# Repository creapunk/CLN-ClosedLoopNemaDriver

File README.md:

# CLN17 - CLOSED-LOOP DRIVER FOR NEMA17

[CLN17 cncept video](http://www.youtube.com/watch?v=A67UROq0t6Q)

# Project Overview

The CLN17 motor driver is an **open-source**, compact, high-performance closed-loop stepper motor driver designed specifically for NEMA17 form factor motors. The driver offers advanced features such as silent and smooth motion, high-precision position control, and energy-saving capabilities, making it ideal for various applications, including robotics, CNC machines, and 3D printers. 

Detailed documentation at [creapunk.com](https://creapunk.com)!

## Board Diagram

## Key Features

- 🕹️ **Closed-Loop Control:** Enables precise motion in challenging conditions.
- 💪 **Adaptive Torque Control:** Optimizes energy efficiency, reduces stress, and extends motor lifespan.
- 🧩 **Reliable Operation and Enhanced Safety:** Ensures reliable operation and protects users from potential harm.
- 🛡️ **Modular Concept:** Provides flexibility and cost-effectiveness through various configurations and expansion boards.

## Key Specs

- 🔌 **Wide Input Voltage Range:** 5-25VDC with reverse polarity and surge protection
- ⚡️ **Powerful Motor Control:** 1.4A RMS current per phase with up to 2.5A peak and up to 1/256 microstepping
- 🚀 **High-Performance MCU:** STM32G431CB Arm Cortex-M4 running at 170MHz with Classic EN/DIR/STEP interface, CAN-Bus, I2C, UART and USB Type-C with PD2.0 support,
- 🔒 **Compact and Durable Design:** 38x38mm PCB, with optional aluminum housing for heat dissipation and mechanical protection and minimal height of 7.5mm (10mm with connectors)

## Applications

- 🎓 Learning Platforms
- 🛠️ CNC Machines & 3D printers
- 🤖 Robotics & Automation Systems
- 🤝 Collaborative Robots
- 🔭 Camera & Telescope Stabilization Systems
- 🔬 Laboratory Equipment
- 🏭 Industrial Motion Control Systems
- 📳 Haptics & Force Feedback Systems

------

### Support the Project!

**If you like the project and want to support its development, you can do so through:**

- **[Ko-fi](https://ko-fi.com/creapunk)** (*preferred for membership subscription and one-time donation*) - here, you can sign up for monthly support, or you can make a one-time donation as well!
- **[Patreon](http://patreon.com/creapunk)** - similar to Ko-fi, but with higher fees.

Don't forget to join **[creapunk community on Discord](https://discord.gg/4uFSsffhMt)** for the latest updates and discussions!

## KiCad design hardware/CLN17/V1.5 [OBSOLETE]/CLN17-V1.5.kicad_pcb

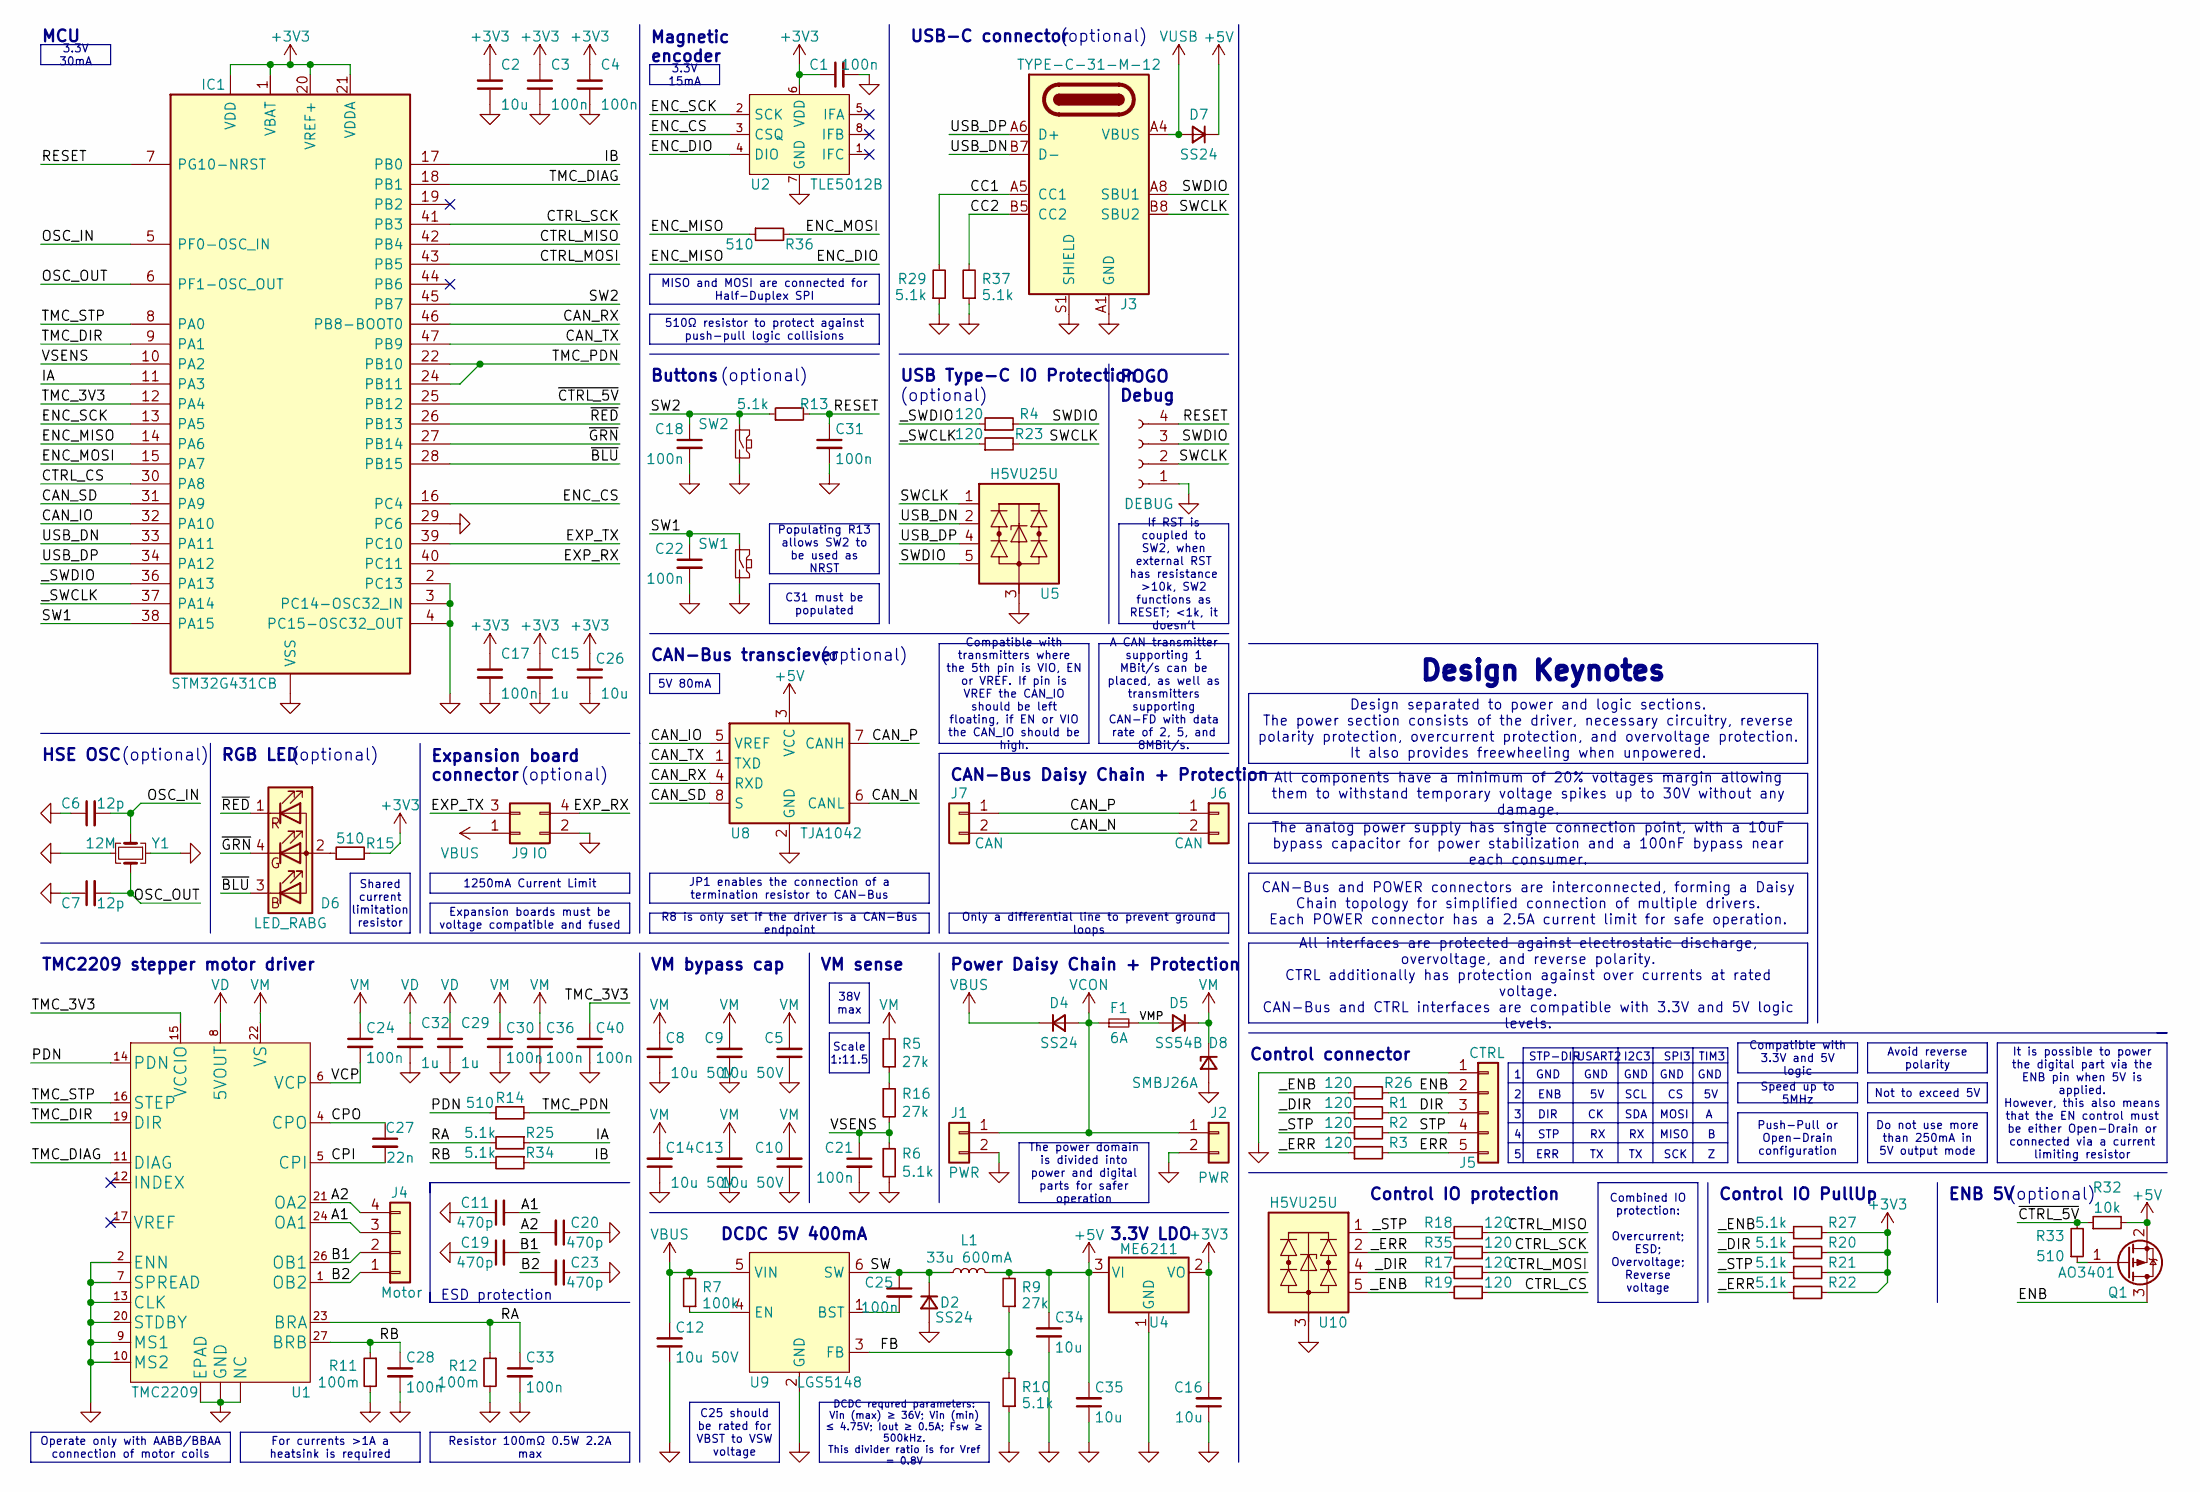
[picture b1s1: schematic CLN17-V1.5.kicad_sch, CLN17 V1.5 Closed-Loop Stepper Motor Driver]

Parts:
C1, C3, C4, C17, C18, C21, C22, C24, C28, C30, C31, C33, C36, C40: 100n; C0402; Part Type Basic; LCSC Part # C307331
C2, C16, C26, C34, C35: 10u; C0402; Part Type Basic; LCSC Part # C15525
C5, C8, C9, C10, C12, C13, C14: 10u 50V; C_1206_3216Metric; Part Type Basic; LCSC Part # C13585
C6, C7: 12p; C0402; Part Type Basic; LCSC Part # C1547
C11, C19, C20, C23: 470p; C0402; Part Type Basic; LCSC Part # C1537
C15, C29, C32: 1u; C0402; Part Type Basic; LCSC Part # C52923
C25: 100n; C0402; Part Type Basic; LCSC Part # C1525
C27: 22n; C0402; Part Type Basic; LCSC Part # C1532
D2, D4, D7: SS24; D_SOD-123F; Part Type Extended; LCSC Part # C2827931
D5: SS54B; D_SMB; Part Type Extended; LCSC Part # C3011125
D6: LED_RABG; LED_RGB_0606; Part Type Extended; LCSC Part # C2874115
D8: SMBJ26A; D_SMB; Part Type Extended; LCSC Part # C726831
F1: 6A; R1206_Shunt; Part Type Extended; LCSC Part # C183157
IC1: STM32G431CB; QFN-48-1EP_7x7mm_P0.5mm_EP5.6x5.6mm; Part Type Extended; LCSC Part # C529356
J1, J2: PWR; XH2.54 2P; Part Type Extended; LCSC Part # C2908611
J3: TYPE-C-31-M-12; USB-TYPE-C-31-M-12; Part Type Extended; LCSC Part # C2988369
J4: Motor; XH2.54 4P; Part Type Extended; LCSC Part # C21273
J5: CTRL; PH2.0 5P; Part Type Extended; LCSC Part # C2908637
J6, J7: CAN; PH2.0 2P; Part Type Extended; LCSC Part # C2908634
J8: DEBUG; SWD; Part Type -----
J9: IO; 2x2P2.00mm_Vertical_SMD; Part Type Extended; LCSC Part # C2911301
L1: 33u 600mA; CD32; Part Type Extended; LCSC Part # C492262
Q1: AO3401; SOT-23-3; Part Type Basic; LCSC Part # C15127
R1, R2, R3, R4, R17, R18, R19, R23, R26, R35: 120; R0402; Part Type Basic; LCSC Part # C25079
R5, R9, R16: 27k; R0402; Part Type Basic; LCSC Part # C25771
R6, R10, R13, R20, R21, R22, R25, R27, R29, R34, R37: 5.1k; R0402; Part Type Basic; LCSC Part # C25941
R7: 100k; R0402; Part Type Basic; LCSC Part # C25741
R11, R12: 100m; R1206_Shunt; Part Type Extended; LCSC Part # C7467250
R14, R15, R33, R36: 510; R0402; Part Type Basic; LCSC Part # C25123
R32: 10k; R0402; Part Type Basic; LCSC Part # C25744
SW1, SW2: SW_Push; SW_SPST_PTS810; Part Type Extended; LCSC Part # C2888427
U1: TMC2209; QFN-28-termal; Part Type Extended; LCSC Part # C465949
U2: TLE5012B; SOIC-8_3.9x4.9mm_P1.27mm; Part Type Extended; LCSC Part # C123083
U4: ME6211; SOT-23-3; Part Type Basic; LCSC Part # C168807
U5, U10: H5VU25U; DFN-2510; Part Type Basic; JLC Rotation Offset 270
U8: TJA1042; HVSON-8-1EP_3x3mm_P0.65mm_EP1.6x2.4mm; Part Type Extended; LCSC Part # C131480
U9: LGS5148; SOT-23-6; Part Type Extended; LCSC Part # C5123972
Y1: 12M; Crystal-3225-4P; Part Type Basic; LCSC Part # C9002

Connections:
+3V3: C1.1, C2.2, C3.1, C4.1, C15.1, C16.2, C17.1, C26.2, IC1.1 (VBAT), IC1.20 (VREF+), IC1.21 (VDDA), IC1.23 (VDD), IC1.35 (VDD), IC1.48 (VDD), R15.2, R20.2, R21.2, R22.2, R27.2, U2.6 (VDD), U4.2 (VO)
+5V: C34.2, C35.2, D7.1 (K), L1.2, Q1.2 (S), R9.2, R32.2, U4.3 (VI), U8.3 (VCC)
/A1: C11.2, J4.3, U1.24 (OA1)
/A2: C20.2, J4.4, U1.21 (OA2)
/B1: C19.2, J4.2, U1.26 (OB1)
/B2: C23.2, J4.1, U1.1 (OB2)
/CAN_IO: IC1.32 (PA10), U8.5 (VREF)
/CAN_N: J6.2, J7.2, U8.6 (CANL)
/CAN_P: J6.1, J7.1, U8.7 (CANH)
/CAN_RX: IC1.46 (PB8-BOOT0), U8.4 (RXD)
/CAN_SD: IC1.31 (PA9), U8.8 (S)
/CAN_TX: IC1.47 (PB9), U8.1 (TXD)
/CC1: J3.A5 (CC1), R29.2
/CC2: J3.B5 (CC2), R37.2
/CPI: C27.2, U1.5 (CPI)
/CPO: C27.1, U1.4 (CPO)
/CTRL_CS: IC1.30 (PA8), R19.1
/CTRL_MISO: IC1.42 (PB4), R18.1
/CTRL_MOSI: IC1.43 (PB5), R17.1
/CTRL_SCK: IC1.41 (PB3), R35.1
/DIR: J5.3, R1.2
/ENB: J5.2, Q1.3 (D), R26.2
/ENC_CS: IC1.16 (PC4), U2.3 (CSQ)
/ENC_DIO: IC1.14 (PA6), R36.1, U2.4 (DIO)
/ENC_MOSI: IC1.15 (PA7), R36.2
/ENC_SCK: IC1.13 (PA5), U2.2 (SCK)
/ERR: J5.5, R3.2
/EXP_RX: IC1.40 (PC11), J9.4
/EXP_TX: IC1.39 (PC10), J9.3
/FB: R9.1, R10.2, U9.3 (FB)
/IA: IC1.11 (PA3), R25.1
/IB: IC1.17 (PB0), R34.1
/OSC_IN: C6.2, IC1.5 (PF0-OSC_IN), Y1.1
/OSC_OUT: C7.2, IC1.6 (PF1-OSC_OUT), Y1.3
/PDN: R14.1, U1.14 (PDN)
/RA: C33.1, R12.1, R25.2, U1.23 (BRA)
/RB: C28.1, R11.1, R34.2, U1.27 (BRB)
/RESET: C31.1, IC1.7 (PG10-NRST), J8.4, R13.2
/STP: J5.4, R2.2
/SW: C25.1, D2.1 (K), L1.1, U9.6 (SW)
/SW1: C22.1, IC1.38 (PA15), SW1.1
/SW2: C18.1, IC1.45 (PB7), R13.1, SW2.1
/SWCLK: J3.B8 (SBU2), J8.2, R23.2, U5.1 (I/O1), U5.10
/SWDIO: J3.A8 (SBU1), J8.3, R4.2, U5.5 (I/O4), U5.6 (I/O4)
/TMC_3V3: C40.1, IC1.12 (PA4), U1.15 (VCCIO)
/TMC_DIAG: IC1.18 (PB1), U1.11 (DIAG)
/TMC_DIR: IC1.9 (PA1), U1.19 (DIR)
/TMC_PDN: IC1.22 (PB10), IC1.24 (PB11), R14.2
/TMC_STP: IC1.8 (PA0), U1.16 (STEP)
/USB_DN: IC1.33 (PA11), J3.A7 (D-), J3.B7 (D-), U5.2 (I/O2), U5.9 (I/O2)
/USB_DP: IC1.34 (PA12), J3.A6 (D+), J3.B6 (D+), U5.4 (I/O3), U5.7 (I/O3)
/VCP: C24.2, U1.6 (VCP)
/VMP: D5.2 (A), F1.2
/VSENS: C21.1, IC1.10 (PA2), R6.1, R16.2
/_DIR: R1.1, R17.2, R20.1, U10.4 (I/O3), U10.7 (I/O3)
/_ENB: R19.2, R26.1, R27.1, U10.5 (I/O4), U10.6 (I/O4)
/_ERR: R3.1, R22.1, R35.2, U10.2 (I/O2), U10.9 (I/O2)
/_STP: R2.1, R18.2, R21.1, U10.1 (I/O1), U10.10
/_SWCLK: IC1.37 (PA14), R23.1
/_SWDIO: IC1.36 (PA13), R4.1
/~BLU: D6.3 (BK), IC1.28 (PB15)
/~CTRL_5V: IC1.25 (PB12), R32.1, R33.2
/~GRN: D6.4 (GK), IC1.27 (PB14)
/~RED: D6.1 (RK), IC1.26 (PB13)
GND: C1.2, C2.1, C3.2, C4.2, C5.1, C6.1, C7.1, C8.1, C9.1, C10.1, C11.1, C12.1, C13.1, C14.1, C15.2, C16.1, C17.2, C18.2, C19.1, C20.1, C21.2, C22.2, C23.1, C26.1, C28.2, C29.2, C30.2, C31.2, C32.2, C33.2, C34.1, C35.1, C36.2, C40.2, D2.2 (A), D8.2 (A), IC1.2 (PC13), IC1.3 (PC14-OSC32_IN), IC1.4 (PC15-OSC32_OUT), IC1.29 (PC6), IC1.49 (VSS), J1.2, J2.2, J3.A1 (GND), J3.A12 (GND), J3.B1 (GND), J3.B12 (GND), J3.S1 (SHIELD), J5.1, J8.1, J9.2, R6.2, R10.1, R11.2, R12.2, R29.1, R37.1, SW1.2, SW2.2, U1.2 (ENN), U1.3 (GND), U1.7 (SPREAD), U1.9 (MS1), U1.10 (MS2), U1.13 (CLK), U1.18 (GND), U1.20 (STDBY), U1.25 (NC), U1.29 (EPAD), U2.7 (GND), U4.1 (GND), U5.3 (GND), U5.8 (GND), U8.2 (GND), U8.9 (GND), U9.2 (GND), U10.3 (GND), U10.8 (GND), Y1.2, Y1.4
unnamed: D6.2 (A), R15.1
unnamed: Q1.1 (G), R33.1
unnamed: R5.2, R16.1
unnamed: C25.2, U9.1 (BST)
unnamed: R7.1, U9.4 (EN)
VBUS: C12.2, D4.1 (K), J9.1, R7.2, U9.5 (VIN)
VCON: D4.2 (A), F1.1, J1.1, J2.1
VD: C29.1, C32.1, U1.8 (5VOUT)
VM: C5.2, C8.2, C9.2, C10.2, C13.2, C14.2, C24.1, C30.1, C36.1, D5.1 (K), D8.1 (K), R5.1, U1.22 (VS), U1.28 (VS)
VUSB: D7.2 (A), J3.A4 (VBUS), J3.A9 (VBUS), J3.B4 (VBUS), J3.B9 (VBUS)

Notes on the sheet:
Combined IO protection: Overcurrent; ESD; Overvoltage; Reverse voltage
Do not use more than 250mA in 5V output mode
3.3V 30mA
A CAN transmitter supporting 1 MBit/s can be placed, as well as transmitters supporting CAN-FD with data rate of 2, 5, and 8MBit/s.
If RST is coupled to SW2, when external RST has resistance >10k, SW2 functions as RESET; <1k, it doesn't
R8 is only set if the driver is a CAN-Bus endpoint
The power domain is divided into power and digital parts for safer operation
C31 must be populated
Speed up to 5MHz
Design separated to power and logic sections. The power section consists of the driver, necessary circuitry, reverse polarity protection, overcurrent protection, and overvoltage protection. It also provides freewheeling when unpowered.
JP1 enables the connection of a termination resistor to CAN-Bus
Shared current limitation resistor
Expansion boards must be voltage compatible and fused
Compatible with 3.3V and 5V logic
It is possible to power the digital part via the ENB pin when 5V is applied. However, this also means that the EN control must be either Open-Drain or connected via a current limiting resistor
C25 should be rated for VBST to VSW voltage
38V max
Scale 1:11.5
Compatible with transmitters where the 5th pin is VIO, EN or VREF. If pin is VREF the CAN_IO should be left floating, if EN or VIO the CAN_IO should be high.
3.3V 15mA
All interfaces are protected against electrostatic discharge, overvoltage, and reverse polarity. CTRL additionally has protection against over currents at rated voltage. CAN-Bus and CTRL interfaces are compatible with 3.3V and 5V logic levels.
5V 80mA
Populating R13 allows SW2 to be used as NRST
All components have a minimum of 20% voltages margin allowing them to withstand temporary voltage spikes up to 30V without any damage.
1250mA Current Limit
Push-Pull or Open-Drain configuration
Operate only with AABB/BBAA connection of motor coils
Resistor 100mΩ 0.5W 2.2A max
DCDC requred parameters: Vin (max) ≥ 36V; Vin (min) ≤ 4.75V; Iout ≥ 0.5A; Fsw ≥ 500kHz. This divider ratio is for Vref = 0.8V
Not to exceed 5V
510Ω resistor to protect against push-pull logic collisions
CAN-Bus and POWER connectors are interconnected, forming a Daisy Chain topology for simplified connection of multiple drivers. Each POWER connector has a 2.5A current limit for safe operation.
Only a differential line to prevent ground loops
The analog power supply has single connection point, with a 10uF bypass capacitor for power stabilization and a 100nF bypass near each consumer.
For currents >1A a heatsink is required
MISO and MOSI are connected for Half-Duplex SPI
Avoid reverse polarity
STP-DIR
CAN-Bus Daisy Chain + Protection
(optional)

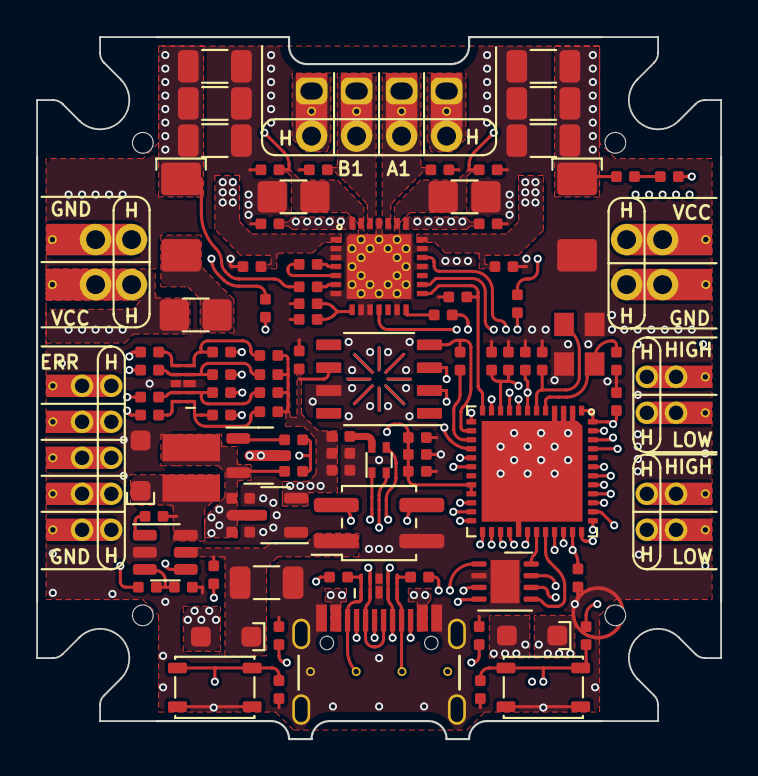
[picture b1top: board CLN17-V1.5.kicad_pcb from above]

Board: 4 copper layers, 38.0 x 39.0 mm, 98 parts (1 on the bottom side), 75 nets.

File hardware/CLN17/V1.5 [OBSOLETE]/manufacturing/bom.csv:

Designator,Footprint,Quantity,Value,LCSC Part #
"C1, C17, C18, C21, C22, C24, C28, C3, C30, C31, C33, C36, C4, C40",C0402,14,100n,C307331
"C10, C12, C13, C14, C5, C8, C9",1206,7,10u 50V,C13585
"C11, C19, C20, C23",C0402,4,470p,C1537
"C15, C29, C32",C0402,3,1u,C52923
"C16, C2, C26, C34, C35",C0402,5,10u,C15525
C25,C0402,1,100n,C1525
C27,C0402,1,22n,C1532
"C6, C7",C0402,2,12p,C1547
"D2, D4, D7",D_SOD-123F,3,SS24,C2827931
D5,D_SMB,1,SS54B,C3011125
D6,LED_RGB_0606,1,LED_RABG,C2874115
D8,D_SMB,1,SMBJ26A,C726831
F1,R1206_Shunt,1,6A,C183157
IC1,QFN-48-1EP_7x7mm_P0.5mm_EP5.6x5.6mm,1,STM32G431CB,C529356
"J1, J2",XH2.54 2P,2,PWR,C2908611
J3,USB-TYPE-C-31-M-12,1,TYPE-C-31-M-12,C2988369
J4,XH2.54 4P,1,Motor,C21273
J5,PH2.0 5P,1,CTRL,C2908637
"J6, J7",PH2.0 2P,2,CAN,C2908634
J9,2x2P2.00mm_Vertical_SMD,1,IO,C2911301
L1,CD32,1,33u 600mA,C492262
Q1,SOT-23-3,1,AO3401,C15127
"R1, R17, R18, R19, R2, R23, R26, R3, R35, R4",R0402,10,120,C25079
"R10, R13, R20, R21, R22, R25, R27, R29, R34, R37, R6",R0402,11,5.1k,C25941
"R11, R12",R1206_Shunt,2,100m,C7467250
"R14, R15, R33, R36",R0402,4,510,C25123
"R16, R5, R9",R0402,3,27k,C25771
R32,R0402,1,10k,C25744
R7,R0402,1,100k,C25741
"SW1, SW2",SW_SPST_PTS810,2,SW_Push,C2888427
U1,QFN-28-termal,1,TMC2209,C465949
"U10, U5",DFN-2510,2,H5VU25U,C7420374
U2,SOIC-8_3.9x4.9mm_P1.27mm,1,TLE5012B,C123083
U4,SOT-23-3,1,ME6211,C168807
U8,HVSON-8-1EP_3x3mm_P0.65mm_EP1.6x2.4mm,1,TJA1042,C131480
U9,SOT-23-6,1,LGS5148,C5123972
Y1,Crystal-3225-4P,1,12M,C9002

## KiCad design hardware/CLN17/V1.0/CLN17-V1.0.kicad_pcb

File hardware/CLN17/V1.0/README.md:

# CLN17 V1 Notes

> #### Attention!
>
> This board has been tested, and the functionality of its main components has been confirmed. However, the board has several issues.
>
> You can proceed with its production, but it's recommended to wait for the updated version with all corrections. By using these files, you acknowledge and understand that:
>
> - This version is released for preview purposes only and will not receive future support.
> - Any use of this version is at your own risk. The author is not responsible for any damage caused by the malfunction of this driver version.
> - Subsequent versions may have changes in the BoM and the layout of all board components, including connectors.

#### Known hardware issues:

- Unstable operation when powered from 4.5 to 5.7V. 
	Minor changes have been made to the circuit and the board that might theoretically fix this issue, but the problem may still arise. This might eliminate the possibility of powering solely through Type-C.
- NRST couldn't be reconfigured to function as a user button. This might be fixable through software.
- Incomplete UCPD interface

#### Known software issues:

- The CAN-Bus transceiver physically operates and produces a differential signal, but its software functionality hasn't been tested
- The IMU seems responsive, but the entire library might need to be rewritten for half-duplex SPI operation

#### Not tested:

- The operation of the external HSE crystal and the dependent RTC

#### V1.01 fixes [Nov 2023]:

- Optimised circuit power supply: 
	- Improved power polygon layout; 
	- Improved DCDC converter layout
- Improved Type-C compatibility: 
	- Added full-featured UCPD interface; 
	- Added 5.1k resistors in case UCPD doesn't work
- Optimised components:
	- ESD protection reduced form factor; 
	- Correct USB Type-C connector with both CC lines

#### V1.02 fixes [Dec 2023]:

- Changed 5V and 3.3V supply capacitor ratings from 2.2uF to 22uF
- Changed the crystal from 8MHz to 12MHz to be identical to V1.5 and V2. 
- Changed HSE load capacitors from 22pF to 12pF
- Removed IMU cause it was conflicting with encoder operation

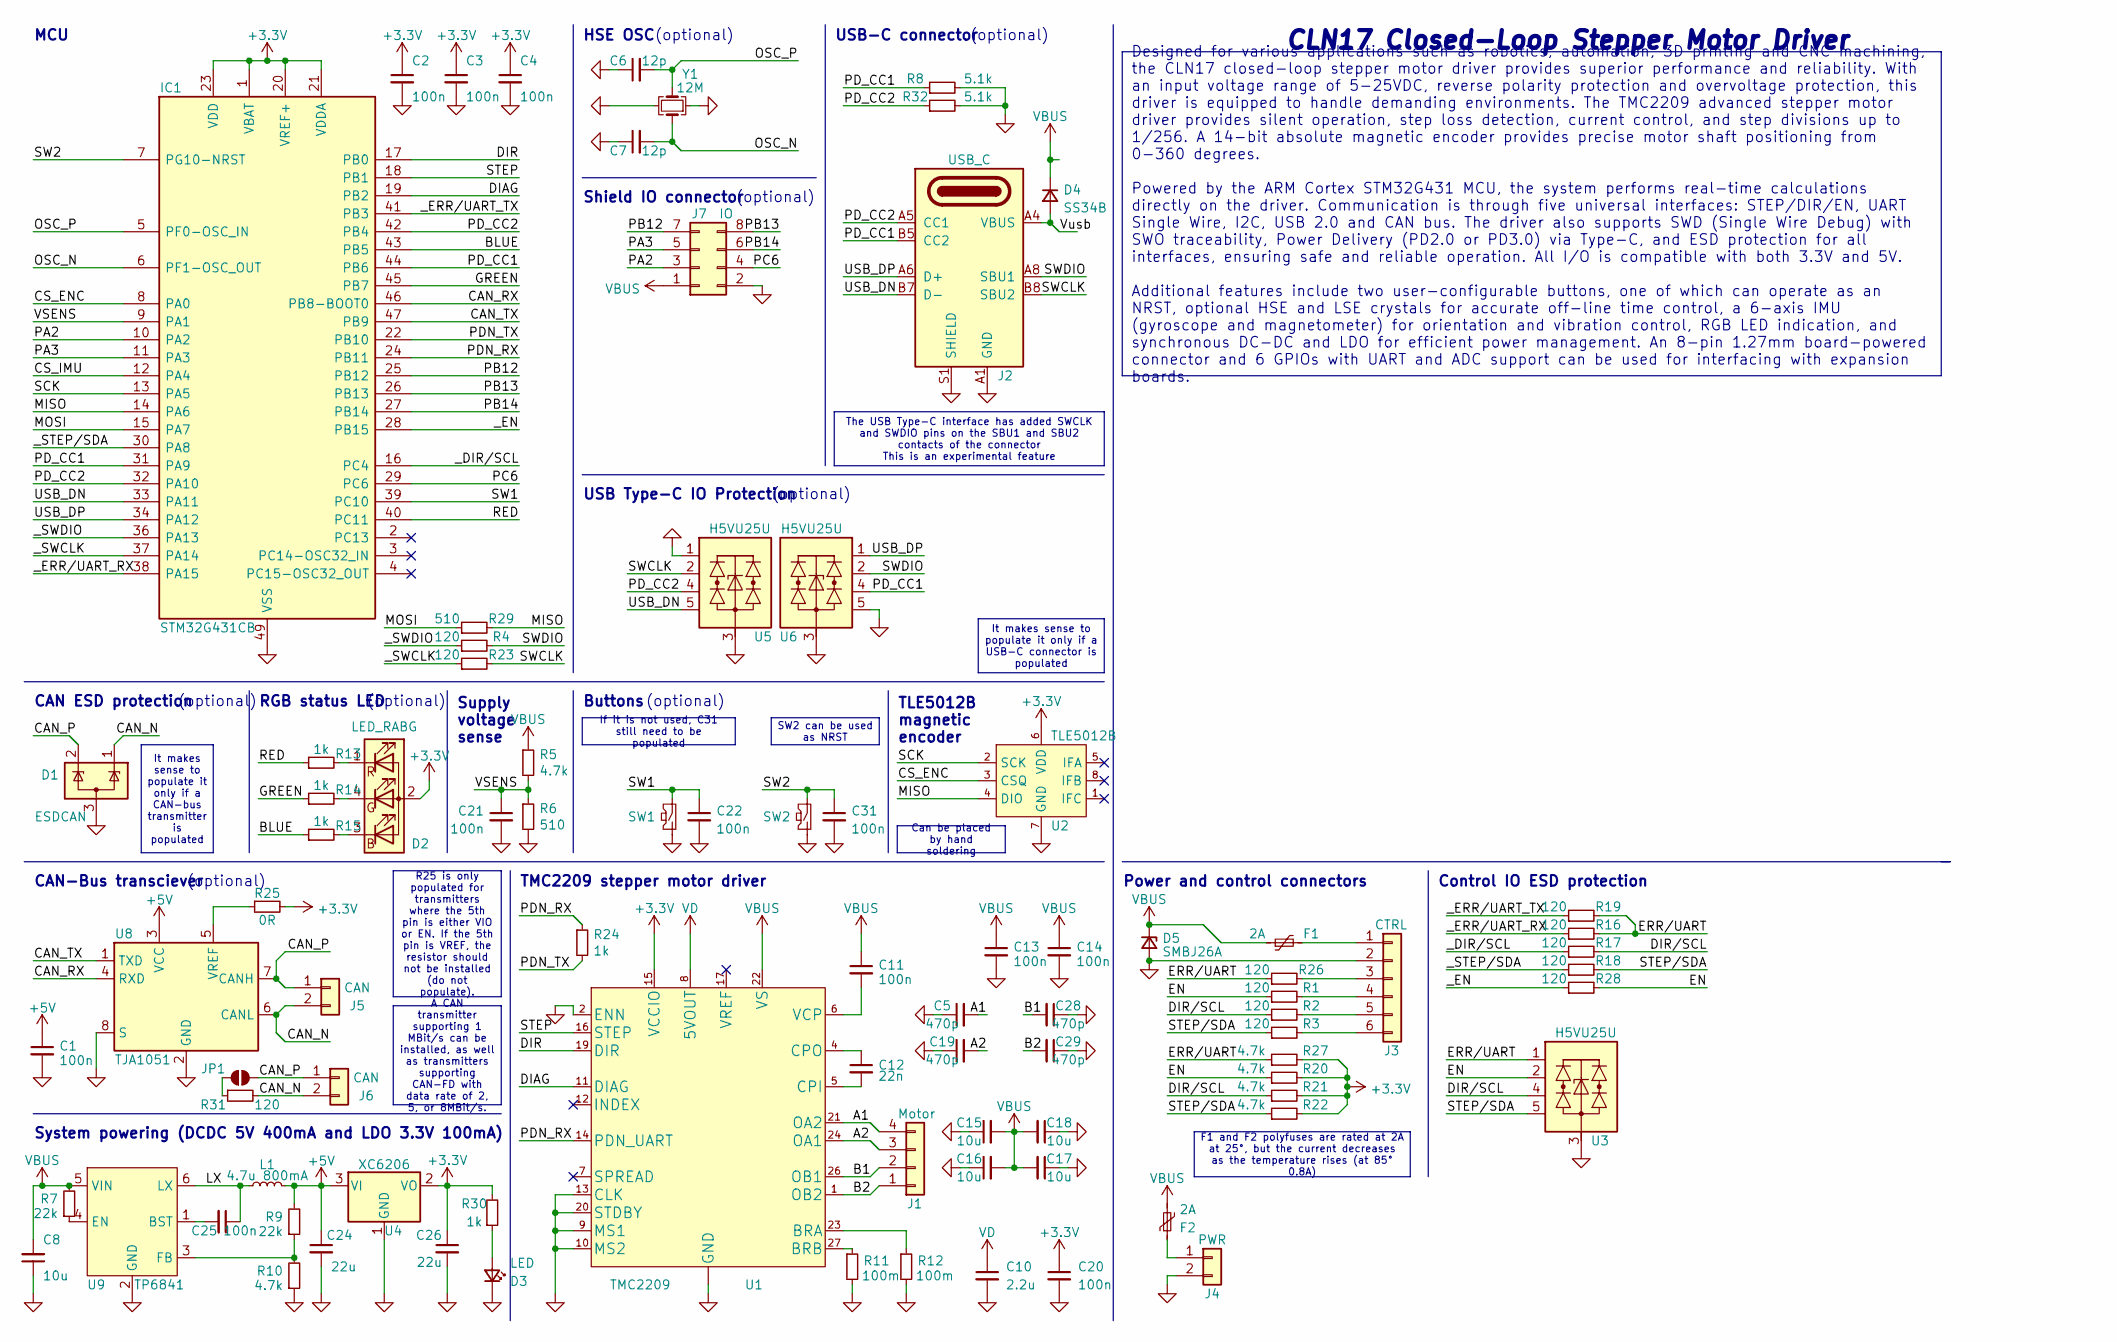
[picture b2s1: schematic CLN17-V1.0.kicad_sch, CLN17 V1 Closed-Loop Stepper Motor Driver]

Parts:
C1, C2, C3, C4, C11, C13, C14, C20, C21, C22, C25, C31: 100n; C0402; LCSC Part # C307331
C5, C19, C28, C29: 470p; C0402; LCSC Part # C1537
C6, C7: 12p; C0402; LCSC Part # C1547
C8, C15, C16, C17, C18: 10u; C_1206_3216Metric; LCSC Part # C13585
C10: 2.2u; C_0603_1608Metric; LCSC Part # C23630
C12: 22n; C0402; LCSC Part # C1532
C24, C26: 22u; C_0603_1608Metric; LCSC Part # C59461
D1: ESDCAN; SOT-23-3; LCSC Part # C2937021
D2: LED_RABG; LED_RGB_0606; LCSC Part # C2874115
D3: LED; LED_0603_1608Metric; LCSC Part # C72043
D4: SS34B; D_SMB; LCSC Part # C13762
D5: SMBJ26A; D_SMB; LCSC Part # C708006
F1, F2: 2A; Fuse_1812_4532Metric; LCSC Part # C960026
IC1: STM32G431CB; QFN-48-1EP_7x7mm_P0.5mm_EP5.6x5.6mm; LCSC Part # C529356
J1: Motor; XH2.54 4P; LCSC Part # C722872
J2: USB_C; USB-TYPE-C-31-M-12-SWD; LCSC Part # C963413
J3: CTRL; XH2.54 6P; LCSC Part # C722881
J4: PWR; XH2.54 2P; LCSC Part # C722860
J5, J6: CAN; PH2.0 2P; LCSC Part # C2908634
J7: IO; PinSocket_2x04_P1.27mm_Vertical; LCSC Part # C509139
JP1: SolderJumper_2_Open; SolderJumper
L1: 4.7u 800mA; L_0805_2012Metric; LCSC Part # C63166
R1, R2, R3, R4, R16, R17, R18, R19, R23, R26, R28, R31: 120; R0402; LCSC Part # C25079
R5, R10, R20, R21, R22, R27: 4.7k; R0402; LCSC Part # C25900
R6, R29: 510; R0402; LCSC Part # C25123
R7, R9: 22k; R0402; LCSC Part # C25768
R8, R32: 5.1k; R0402; LCSC Part # C25905
R11, R12: 100m; R_1206_3216Metric; LCSC Part # C25334
R13, R14, R15, R24, R30: 1k; R0402; LCSC Part # C11702
R25: 0R; R0402; LCSC Part # C17168
SW1, SW2: SW_Push; SW_SPST_PTS810; LCSC Part # C2888427
U1: TMC2209; QFN-28-termal; LCSC Part # C465949
U2: TLE5012B; SOIC-8_3.9x4.9mm_P1.27mm; LCSC Part # C123083
U3, U5, U6: H5VU25U; DFN-2510; JLC Rotation Offset 270
U4: XC6206; SOT-23-3; LCSC Part # C5446
U8: TJA1051; SOIC-8_3.9x4.9mm_P1.27mm; LCSC Part # C92211
U9: TP6841; SOT-23-6; LCSC Part # C2844736
Y1: 12M; Crystal-3225-4P; LCSC Part # C9002

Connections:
+3V3: C2.1, C3.1, C4.1, C20.1, C26.1, D2.2 (A), IC1.1 (VBAT), IC1.20 (VREF+), IC1.21 (VDDA), IC1.23 (VDD), IC1.35 (VDD), IC1.48 (VDD), R20.2, R21.2, R22.2, R25.2, R27.2, R30.2, U1.15 (VCCIO), U2.6 (VDD), U4.2 (VO)
+5V: C1.1, C24.1, L1.2, R9.2, U4.3 (VI), U8.3 (VCC)
/A1: C5.2, J1.4, U1.21 (OA2)
/A2: C19.2, J1.3, U1.24 (OA1)
/B1: C28.2, J1.2, U1.26 (OB1)
/B2: C29.2, J1.1, U1.1 (OB2)
/BLUE: IC1.43 (PB5), R15.1
/CAN_N: D1.1 (K), J5.2, J6.2, R31.2, U8.6 (CANL)
/CAN_P: D1.2 (K), J5.1, J6.1, JP1.2 (B), U8.7 (CANH)
/CAN_RX: IC1.46 (PB8-BOOT0), U8.4 (RXD)
/CAN_TX: IC1.47 (PB9), U8.1 (TXD)
/CS_ENC: IC1.8 (PA0), U2.3 (CSQ)
/CS_IMU: IC1.12 (PA4)
/DIAG: IC1.19 (PB2), U1.11 (DIAG)
/DIR: IC1.17 (PB0), U1.19 (DIR)
/DIR/SCL: R2.1, R17.2, R21.1, U3.4 (I/O3), U3.7 (I/O3)
/EN: R1.1, R20.1, R28.2, U3.2 (I/O2), U3.9 (I/O2)
/ERR/UART: R16.2, R19.2, R26.1, R27.1, U3.1 (I/O1), U3.10
/GREEN: IC1.45 (PB7), R14.1
/LX: C25.1, L1.1, U9.6 (LX)
/MISO: IC1.14 (PA6), R29.2, U2.4 (DIO)
/MOSI: IC1.15 (PA7), R29.1
/OSC_N: C7.2, IC1.6 (PF1-OSC_OUT), Y1.1
/OSC_P: C6.2, IC1.5 (PF0-OSC_IN), Y1.3
/PA2: IC1.10 (PA2), J7.3
/PA3: IC1.11 (PA3), J7.5
/PB12: IC1.25 (PB12), J7.7
/PB13: IC1.26 (PB13), J7.8
/PB14: IC1.27 (PB14), J7.6
/PC6: IC1.29 (PC6), J7.4
/PDN_RX: IC1.24 (PB11), R24.1, U1.14 (PDN_UART)
/PDN_TX: IC1.22 (PB10), R24.2
/PD_CC1: IC1.31 (PA9), IC1.44 (PB6), J2.B5 (CC2), R8.1, U6.4 (I/O3), U6.7 (I/O3)
/PD_CC2: IC1.32 (PA10), IC1.42 (PB4), J2.A5 (CC1), R32.1, U5.4 (I/O3), U5.7 (I/O3)
/RED: IC1.40 (PC11), R13.1
/SCK: IC1.13 (PA5), U2.2 (SCK)
/STEP: IC1.18 (PB1), U1.16 (STEP)
/STEP/SDA: R3.1, R18.2, R22.1, U3.5 (I/O4), U3.6 (I/O4)
/SW1: C22.1, IC1.39 (PC10), SW1.1
/SW2: C31.1, IC1.7 (PG10-NRST), SW2.1
/SWCLK: J2.B8 (SBU2), R23.2, U5.2 (I/O2), U5.9 (I/O2)
/SWDIO: J2.A8 (SBU1), R4.2, U6.2 (I/O2), U6.9 (I/O2)
/USB_DN: IC1.33 (PA11), J2.A7 (D-), J2.B7 (D-), U5.5 (I/O4), U5.6 (I/O4)
/USB_DP: IC1.34 (PA12), J2.A6 (D+), J2.B6 (D+), U6.1 (I/O1), U6.10
/VSENS: C21.1, IC1.9 (PA1), R5.2, R6.1
/Vusb: D4.2 (A), J2.A4 (VBUS), J2.A9 (VBUS), J2.B4 (VBUS), J2.B9 (VBUS)
/_DIR/SCL: IC1.16 (PC4), R17.1
/_EN: IC1.28 (PB15), R28.1
/_ERR/UART_RX: IC1.38 (PA15), R16.1
/_ERR/UART_TX: IC1.41 (PB3), R19.1
/_STEP/SDA: IC1.30 (PA8), R18.1
/_SWCLK: IC1.37 (PA14), R23.1
/_SWDIO: IC1.36 (PA13), R4.1
GND: C1.2, C2.2, C3.2, C4.2, C5.1, C6.1, C7.1, C8.1, C10.2, C13.2, C14.2, C15.1, C16.1, C17.1, C18.1, C19.1, C20.2, C21.2, C22.2, C24.2, C26.2, C28.1, C29.1, C31.2, D1.3 (A), D3.1 (K), D5.2 (A), IC1.49 (VSS), J2.A1 (GND), J2.A12 (GND), J2.B1 (GND), J2.B12 (GND), J2.S1 (SHIELD), J3.2, J4.2, J7.2, R6.2, R8.2, R10.1, R11.2, R12.2, R32.2, SW1.2, SW2.2, U1.2 (ENN), U1.3 (GND), U1.9 (MS1), U1.10 (MS2), U1.13 (CLK), U1.18 (GND), U1.20 (STDBY), U1.25 (NC), U1.29 (EPAD), U2.7 (GND), U3.3 (GND), U3.8 (GND), U4.1 (GND), U5.1 (I/O1), U5.3 (GND), U5.8 (GND), U5.10, U6.3 (GND), U6.5 (I/O4), U6.6 (I/O4), U6.8 (GND), U8.2 (GND), U8.8 (S), U9.2 (GND), Y1.2, Y1.4
unnamed: D2.3 (BK), R15.2
unnamed: D2.4 (GK), R14.2
unnamed: D2.1 (RK), R13.2
unnamed: D3.2 (A), R30.1
unnamed: F1.2, J3.1
unnamed: J3.3, R26.2
unnamed: J3.4, R1.2
unnamed: J3.5, R2.2
unnamed: J3.6, R3.2
unnamed: F2.1, J4.1
unnamed: JP1.1 (A), R31.1
unnamed: R12.1, U1.23 (BRA)
unnamed: R11.1, U1.27 (BRB)
unnamed: C12.2, U1.5 (CPI)
unnamed: C12.1, U1.4 (CPO)
unnamed: C11.2, U1.6 (VCP)
unnamed: R25.1, U8.5 (VREF)
unnamed: C25.2, U9.1 (BST)
unnamed: R7.1, U9.4 (EN)
unnamed: R9.1, R10.2, U9.3 (FB)
VBUS: C8.2, C11.1, C13.1, C14.1, C15.2, C16.2, C17.2, C18.2, D4.1 (K), D5.1 (K), F1.1, F2.2, J7.1, R5.1, R7.2, U1.22 (VS), U1.28 (VS), U9.5 (VIN)
VD: C10.1, U1.8 (5VOUT)

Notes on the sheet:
R25 is only populated for transmitters where the 5th pin is either VIO or EN. If the 5th pin is VREF, the resistor should not be installed (do not populate).
Can be placed by hand soldering
A CAN transmitter supporting 1 MBit/s can be installed, as well as transmitters supporting CAN-FD with data rate of 2, 5, or 8MBit/s.
If it is not used, C31 still need to be populated
The USB Type-C interface has added SWCLK and SWDIO pins on the SBU1 and SBU2 contacts of the connector This is an experimental feature
It makes sense to populate it only if a CAN-bus transmitter is populated
SW2 can be used as NRST
F1 and F2 polyfuses are rated at 2A at 25°, but the current decreases as the temperature rises (at 85° 0.8A)
It makes sense to populate it only if a USB-C connector is populated
Designed for various applications such as robotics, automation, 3D printing and CNC machining, the CLN17 closed-loop stepper motor driver provides superior performance and reliability. With an input voltage range of 5-25VDC, reverse polarity protection and overvoltage protection, this driver is equ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
(optional)
CLN17 Closed-Loop Stepper Motor Driver
TLE5012B magnetic encoder
MCU
CAN-Bus transciever
Power and control connectors
System powering (DCDC 5V 400mA and LDO 3.3V 100mA)
CAN ESD protection
Shield IO connector
USB-C connector
TMC2209 stepper motor driver
Buttons
RGB status LED
Supply voltage sense
HSE OSC
Control IO ESD protection
USB Type-C IO Protection

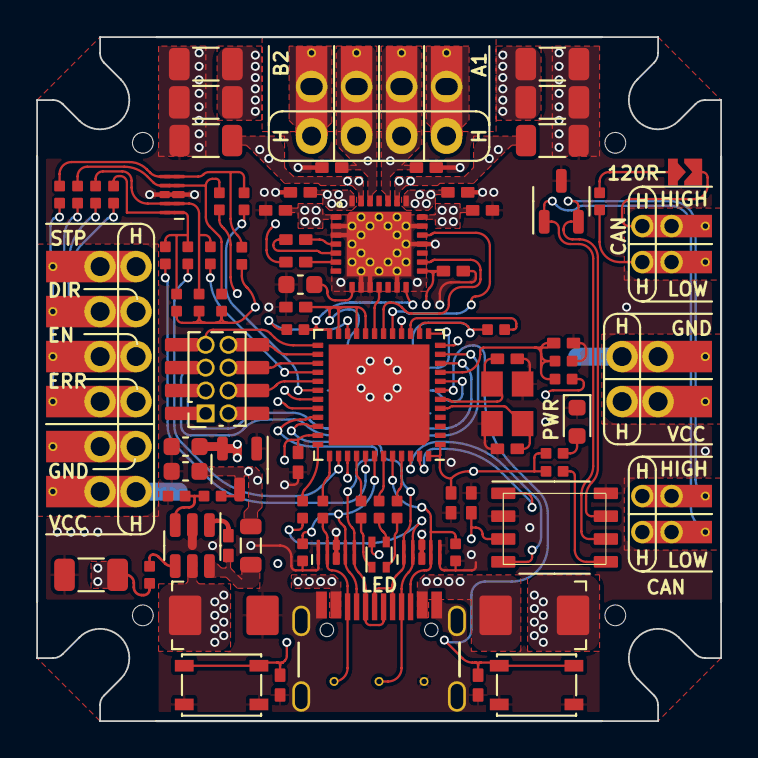
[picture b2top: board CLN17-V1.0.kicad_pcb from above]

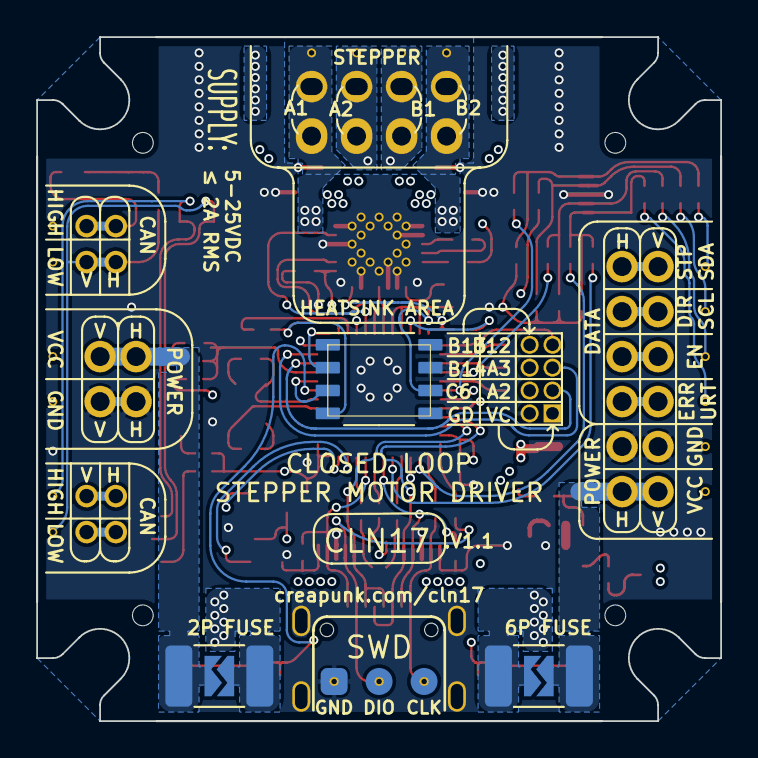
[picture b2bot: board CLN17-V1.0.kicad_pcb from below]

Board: 4 copper layers, 38.0 x 38.0 mm, 87 parts (3 on the bottom side), 75 nets.

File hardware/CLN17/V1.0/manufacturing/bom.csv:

ID	Designator	Footprint	Quantity	Value	LCSC Part #
1	C1, C11, C13, C14, C2, C20, C21, C22, C25, C3, C31, C4	C0402	12	100n	C307331
2	C10	C_0603_1608Metric	1	2.2u	C23630
3	C12	C0402	1	22n	C1532
4	C15, C16, C17, C18, C8	C_1206_3216Metric	5	10u	C13585
5	C19, C28, C29, C5	C0402	4	470p	C1537
6	C24, C26	C_0603_1608Metric	2	22u	C59461
7	C6, C7	C0402	2	12p	C1547
8	D1	SOT-23-3	1	ESDCAN	C2937021
9	D2	LED_RGB_0606	1	LED_RABG	C2874115
10	D3	LED_0603_1608Metric	1	LED	C72043
11	D4	D_SMB	1	SS34B	C13762
12	D5	D_SMB	1	SMBJ26A	C708006
13	F1, F2	Fuse_1812_4532Metric	2	2A	C960026
14	IC1	QFN-48-1EP_7x7mm_P0.5mm_EP5.6x5.6mm	1	STM32G431CB	C529356
15	J1	XH2.54 4P	1	Motor	C722872
16	J2	USB-TYPE-C-31-M-12-SWD	1	USB_C	C963413
17	J3	XH2.54 6P	1	CTRL	C722881
18	J4	XH2.54 2P	1	PWR	C722860
19	J5, J6	PH2.0 2P	2	CAN	C2908634
20	J7	PinSocket_2x04_P1.27mm_Vertical	1	IO	C509139
21	L1	L_0805_2012Metric	1	4.7u 800mA	C63166
22	R1, R16, R17, R18, R19, R2, R23, R26, R28, R3, R31, R4	R0402	12	120	C25079
23	R10, R20, R21, R22, R27, R5	R0402	6	4.7k	C25900
24	R11, R12	R_1206_3216Metric	2	100m	C25334
25	R13, R14, R15, R24, R30	R0402	5	1k	C11702
26	R25	R0402	1	0R	C17168
27	R29, R6	R0402	2	510	C25123
28	R32, R8	R0402	2	5.1k	C25905
29	R7, R9	R0402	2	22k	C25768
30	SW1, SW2	SW_SPST_PTS810	2	SW_Push	C2888427
31	U1	QFN-28-termal	1	TMC2209	C465949
32	U2	SOIC-8_3.9x4.9mm_P1.27mm	1	TLE5012B	C123083
33	U3, U5, U6	DFN-2510	3	H5VU25U	C7420374
34	U4	SOT-23-3	1	XC6206	C5446
35	U8	SOIC-8_3.9x4.9mm_P1.27mm	1	TJA1051	C92211
36	U9	SOT-23-6	1	TP6841	C2844736
37	Y1	Crystal-3225-4P	1	12M	C9002

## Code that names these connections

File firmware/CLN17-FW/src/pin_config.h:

#pragma once

#ifndef PIN_CONFIG_H
#define PIN_CONFIG_H

namespace PINOUT
{
    // Encoder
    constexpr PinName ENC_MOSI = PA_7;
    constexpr PinName ENC_MISO = PA_6;
    constexpr PinName ENC_SCLK = PA_5;
    constexpr PinName ENC_CSEL = PC_4;

    // LED
    constexpr PinName LED_RED = PB_13; // OUTPUT; HIGH = OFF, LOW = ON
    constexpr PinName LED_GRN = PB_14; // OUTPUT; HIGH = OFF, LOW = ON
    constexpr PinName LED_BLU = PB_15; // OUTPUT; HIGH = OFF, LOW = ON

    // Ststem telemetry
    constexpr PinName SYS_VSUP = PA_2;      // INPUT_ANALOG
    constexpr PinName SYS_VREF = PADC_VREF; // Core VREF voltage ADC
    constexpr PinName SYS_TEMP = PADC_TEMP; // Core VTEMP temperature ADC

    // Buttons
    constexpr PinName SYS_SW1 = PA_15; // INPUT_PULLUP; LOW = PRESSED
    constexpr PinName SYS_SW2 = PB_7;  // INPUT_PULLUP; LOW = PRESSED

    // CTRL connector
    constexpr PinName CTRL_ENB = PA_8;  // ENB / 5V / SCL / CS   / 5V
    constexpr PinName CTRL_STP = PB_5;  // DIR / CK / SDA / MOSI / A
    constexpr PinName CTRL_DIR = PB_4;  // STP / RX / RX  / MISO / B
    constexpr PinName CTRL_ERR = PB_3;  // ERR / TX / TX  / SCK  / Z
    constexpr PinName CTRL_5VO = PB_12; // 5V output on ENB, OPEN-DRAIN Logic

    // Expansion connector
    constexpr PinName EXP_TX = PC_10; // UART3 RX
    constexpr PinName EXP_RX = PC_11; // UART3 TX

    // CAN-Bus interface
    constexpr PinName CAN_RX = PB_8;  // Recieve line
    constexpr PinName CAN_TX = PB_9;  // Trancieve line
    constexpr PinName CAN_SD = PA_9;  // Shutdown pin (ACTIVE LOW)
    constexpr PinName CAN_IO = PA_10; // HIGH for (VIO or EN) or HIGH-Z for (VREF)

    // USB interface
    constexpr PinName USB_USB_DP = PA_12;
    constexpr PinName USB_USB_DN = PA_11;

    // Motor Driver (depends on version)
    namespace V1_5 // CLN17 V1.5
    {
        constexpr PinName ISEN_A = PA_3;
        constexpr PinName ISEN_B = PB_0;

        constexpr PinName DRV_RST = PA_4; // Should be HIGH before activating DIAG, DIR, STEP, PDN
        constexpr PinName DRV_ERR = PB_1;

        constexpr PinName DRV_PDN = PB_11; // LPUART1

        constexpr PinName DRV_DIR = PA_0;
        constexpr PinName DRV_STEP = PA_1;


    }

    namespace V2_0 // CLN17 V1.5
    {
        constexpr PinName ISEN_A = PA_3;
        constexpr PinName ISEN_B = PB_0;

        constexpr PinName DRV_RST = PA_4;
        constexpr PinName DRV_ERR = PB_1;

        constexpr PinName DRV_EN = PA_4;
        constexpr PinName DRV_A1 = PA_0;
        constexpr PinName DRV_A2 = PA_1;
        constexpr PinName DRV_B1 = PB_11;
        constexpr PinName DRV_B2 = PB_10;
    }

}

#endif

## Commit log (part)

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2023-05-24 readme, license, todo
2023-10-10 CLN17 V1 Hardware Design Files
    KiCAD project + BoM for LCSC + Gerbers + P&P file + PDF Schematic + STEP 3D model
2023-10-27 V1.1 fixes
    - Optimised circuit power supply:
    - Improved power polygon layout;
    - Improved DCDC converter layout
    - Improved Type-C compatibility:
    - Added full-featured UCPD interface;
    - Added 5.1k resistors in case UCPD doesn't work
2023-12-20 Added block diagrams, schematics and .step files for V1.5 and V2.0
2023-12-28 Create FUNDING.yml
    Added ways to sponsor the project
2023-12-29 Removed outdated README, LICENSE, and wiki
2023-12-29 Updated hardware design structure
2023-12-29 new readme, license, and wiki
2023-12-29 Fixed discord link in readme
2024-01-21 Released CLN17 V1.5 hardware design
2024-01-22 Minor documentation updates
    - added CLN17 V2 information
    - added board diagram for CLN17 V2
    - minor updates to README
    - added board requirements for V1.5
2024-01-27 A bit of firmware, a bit about hardware
    - Added a few notes about manufacturing v1.5 boards
    - Published pinout for V1.5 and V2.0
    - Added TLE5012B register library
    - Added test code for USB + HSE test
    - Other minor changes
2024-03-25 Repo reorganization & updates
    Now the repository only contains wiki and hardware files.
    - Removed firmware (will be moved to a separate repository)
    - Added information about CLN234
    - Fixed markdown syntax error
    - Other minor changes
2024-03-30 CLN17 V2 design improvements
    - Removed CAN-bus termination resistor [the termination resistor will be integrated into the wire to avoid mix-ups]
    - Changed current shunt rating from 20mR to 50mR, amplifier from 50V/V to 20V/V [noise reduction]
    - Removed fuse as the DRV8844 integrated OCP works good enough [optimise price and avoid potential problems]
    - Replaced LDO with a less noisy one, noise reduction improved from 50db@1kHz to 70db@1kHz [noise reduction]
    - Added ferrite to analogue supply [noise reduction]
    - Added pull-up to ground on PC13, PC14, PC15 [software version detection]
2024-03-31 CLN17 V1.5 design improvements
    - Removed CAN-bus termination resistor [the termination resistor will be integrated into the wire to avoid mix-ups]
    - Replaced LDO with a less noisy one, noise reduction improved from 50db@1kHz to 70db@1kHz [noise reduction]
    - Added pull-up to ground on PC6, PC13, PC14, PC15 [software version detection]
2024-06-30 CLN17 V2.0 source files released
    Release of the CLN17 V2.0 source files on the occasion of the completion of the Beta batch production.
2024-07-03 Released enclosure design for CLN17 V1.5 and V2.0
2025-12-09 Release of CLN17 V2.1 and CLN17 V2.5 design files, announce of CLN17 V3.0

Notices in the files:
hardware/CLN17/V1.0/CLN17-V1.0.kicad_sch:
https://creativecommons.org/licenses/by-nc-sa/4.0
